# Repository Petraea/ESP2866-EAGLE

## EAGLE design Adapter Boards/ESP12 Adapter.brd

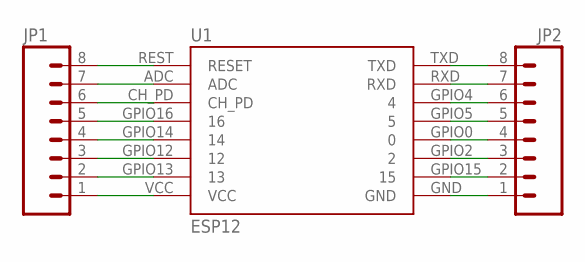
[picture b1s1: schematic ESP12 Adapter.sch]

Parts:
JP1, JP2: M08; 1X08_PIN1_NO_SILK
U1: ESP12

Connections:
unnamed: JP1.1, U1.VCC
unnamed: JP1.2, U1.GPIO13 (13)
unnamed: JP1.3, U1.GPIO12 (12)
unnamed: JP1.4, U1.GPIO14 (14)
unnamed: JP1.5, U1.GPIO16 (16)
unnamed: JP1.6, U1.CH_PD
unnamed: JP1.7, U1.ADC
unnamed: JP1.8, U1.REST (RESET)
unnamed: JP2.8, U1.TXD
unnamed: JP2.7, U1.RXD
unnamed: JP2.6, U1.GPIO4 (4)
unnamed: JP2.5, U1.GPIO5 (5)
unnamed: JP2.4, U1.GPIO0 (0)
unnamed: JP2.3, U1.GPIO2 (2)
unnamed: JP2.2, U1.GPIO15 (15)
unnamed: JP2.1, U1.GND

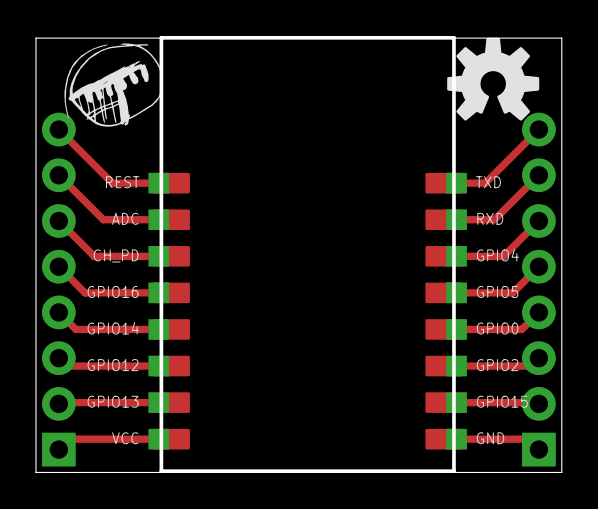
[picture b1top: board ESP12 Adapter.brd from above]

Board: 2 copper layers, 29.0 x 24.1 mm, 5 parts (0 on the bottom side), 16 nets.

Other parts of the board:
U$1: OSHW-LOGO-M
U$2: HARK-S

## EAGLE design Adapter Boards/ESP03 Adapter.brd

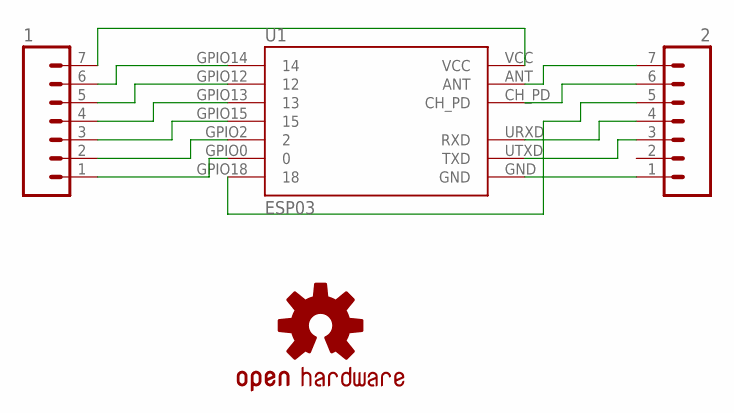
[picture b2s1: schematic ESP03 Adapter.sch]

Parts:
1, 2: M07; 1X07
LOGO1: OSHW-LOGOM; OSHW-LOGO-M
U1: ESP03

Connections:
unnamed: 1.7, U1.VCC
unnamed: 1.6, U1.GPIO14 (14)
unnamed: 1.5, U1.GPIO12 (12)
unnamed: 1.4, U1.GPIO13 (13)
unnamed: 1.3, U1.GPIO15 (15)
unnamed: 1.2, U1.GPIO2 (2)
unnamed: 1.1, U1.GPIO0 (0)
unnamed: 2.7, U1.ANT
unnamed: 2.6, U1.CH_PD
unnamed: 2.5, U1.GPIO18 (18)
unnamed: 2.4, U1.URXD (RXD)
unnamed: 2.3, U1.UTXD (TXD)
unnamed: 2.1, U1.GND

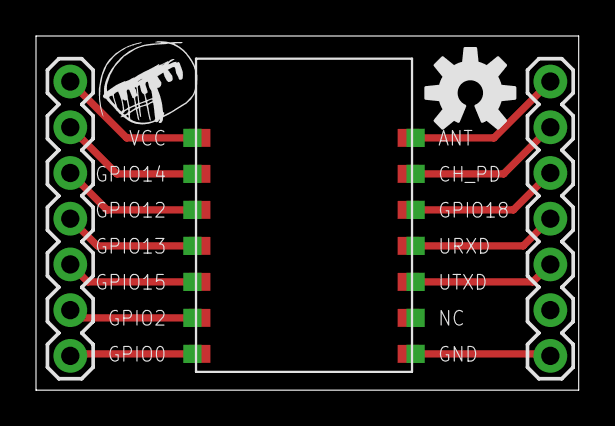
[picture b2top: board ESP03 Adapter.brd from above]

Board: 2 copper layers, 30.1 x 19.7 mm, 5 parts (0 on the bottom side), 13 nets.

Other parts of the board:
E$1: HARK-S

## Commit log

2015-02-08 Adding files
2015-02-13 Update Library
2015-02-13 Adding new ESP03 Adapter board; Fix minor errors in library
2015-02-13 Added OSHW logos
2015-02-13 Added hark logo
2015-02-13 Micronise hark logo; add multiple sizes
2015-02-14 Repair pads; resize ESP12
2015-02-14 Add ESP01 to library

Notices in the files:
parts and their libraries:
SparkFun-Connectors: Licensing: Creative Commons ShareAlike 4.0 International - https://creativecommons.org/licenses/by-sa/4.0
